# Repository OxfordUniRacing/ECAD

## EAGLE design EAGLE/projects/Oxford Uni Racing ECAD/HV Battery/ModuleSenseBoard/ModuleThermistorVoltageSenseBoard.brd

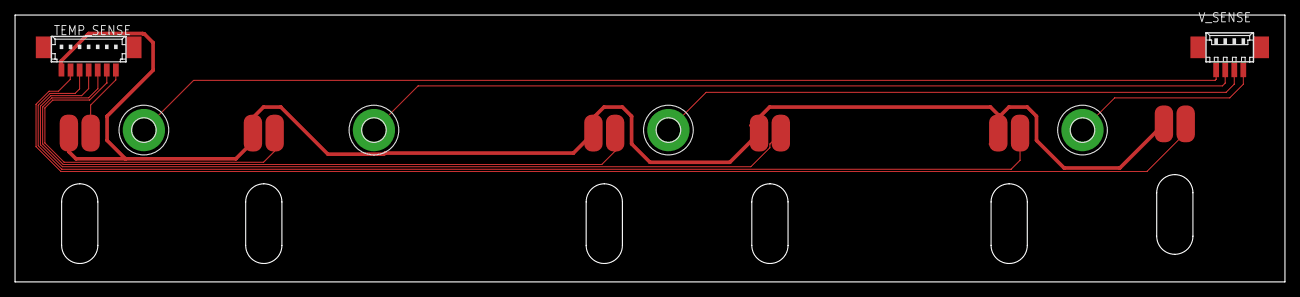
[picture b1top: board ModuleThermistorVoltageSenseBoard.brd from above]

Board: 2 copper layers, 175.3 x 36.8 mm, 12 parts (0 on the bottom side), 11 nets.

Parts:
T1, T2, T3, T4, T5, T6: THERMISTOR_CUTOUT
TEMP_SENSE: 53398-07
V1+, V1-, V2+, V3+: MOUNT-PAD-ROUND3.2; 3,2-PAD
V_SENSE: 53261-04

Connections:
GND: T1.1, T2.1, T3.1, T4.1, T5.1, T6.1, TEMP_SENSE.7
unnamed: T2.2, TEMP_SENSE.2
unnamed: T3.2, TEMP_SENSE.3
unnamed: T4.2, TEMP_SENSE.4
unnamed: T5.2, TEMP_SENSE.5
unnamed: T6.2, TEMP_SENSE.6
TSENSE1: T1.2, TEMP_SENSE.1
V1+: V1+.B3,2, V_SENSE.2
V1-: V1-.B3,2, V_SENSE.1
V2+: V2+.B3,2, V_SENSE.3
V3+: V3+.B3,2, V_SENSE.4

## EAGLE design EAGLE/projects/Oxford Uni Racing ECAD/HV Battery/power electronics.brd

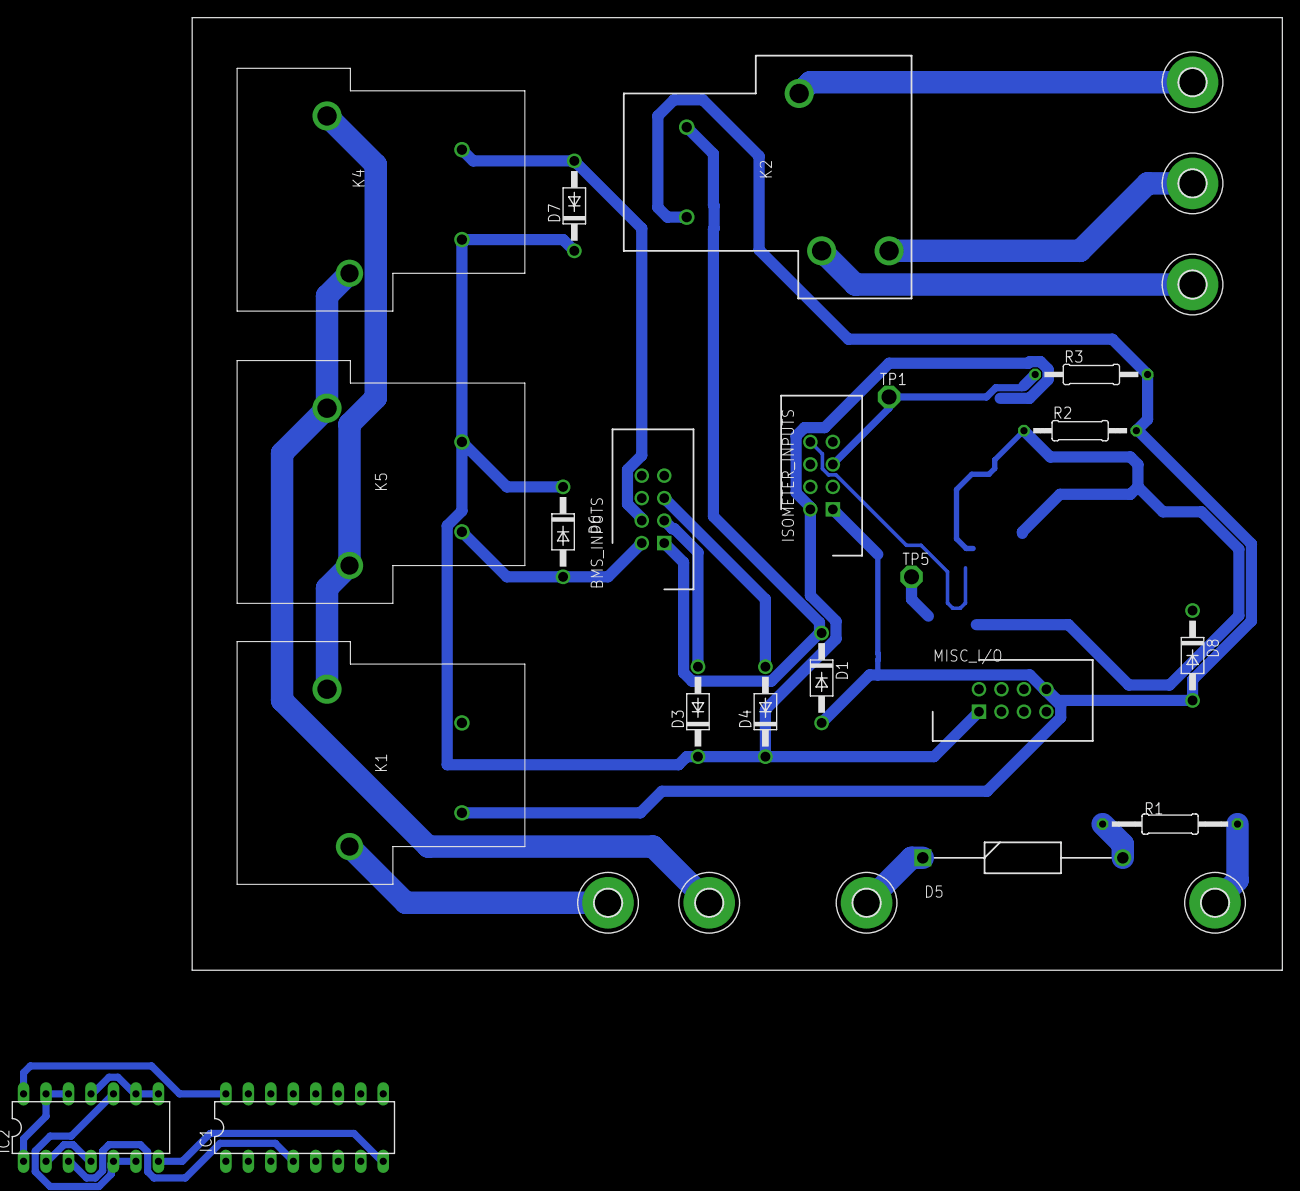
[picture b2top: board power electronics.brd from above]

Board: 2 copper layers, 123.2 x 107.6 mm, 28 parts (0 on the bottom side), 25 nets.

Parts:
BMS_INPUTS: T821108A1S100CEU; HDRV8W64P254_2X4_1778X895X915P
D1, D3, D4, D6, D7, D8: 1N4004; DO41-10
D5: 1N5369BRLG; DIOAD2260W109L864D349
EMSDC: MOUNT-PAD-ROUND3.0; 3,0-PAD
EMSDC_POSAIR-: MOUNT-PAD-ROUND3.0; 3,0-PAD
EMSDC_PRECHARGERELAY-: MOUNT-PAD-ROUND3.0; 3,0-PAD
EMSDC_TSMS+: MOUNT-PAD-ROUND3.0; 3,0-PAD
EMSDC_TSMS-: MOUNT-PAD-ROUND3.0; 3,0-PAD
HV+: MOUNT-PAD-ROUND3.0; 3,0-PAD
HV_INDICATOR: MOUNT-PAD-ROUND3.0; 3,0-PAD
IC1: 4043N; DIL16
IC2: 4001N; DIL14
ISOMETER_INPUTS: T821108A1S100CEU; HDRV8W64P254_2X4_1778X895X915P
K1, K4, K5: T9AS1D12-48=T9A; T9AS1D1248T9A
K2: T9AS5D12-12=T9A; T9AS1D12
MISC_I/O: T821108A1S100CEU; HDRV8W64P254_2X4_1778X895X915P
R1: 3.3K; 0207/15
R2, R3: 2.2K; 0207/12
TP1, TP5: TPSPAD1-17; P1-17

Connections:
+12V: D3.C, D4.C, D6.C, D7.C, IC1.5, ISOMETER_INPUTS.2, K4.2, K5.1, MISC_I/O.1
CHG_SAFE: BMS_INPUTS.2, D6.A, K5.2
DISCHARGE_ENABLE: BMS_INPUTS.4, D7.A, K4.1
EMSDC_IMD+: K1.4, K4.4, K5.3
GND: D1.A, D8.A, IC1.3, ISOMETER_INPUTS.1, K1.2, K2.5, MISC_I/O.8, R2.2, R3.2
unnamed: EMSDC_TSMS-.B3,0, K2.1
unnamed: EMSDC_POSAIR-.B3,0, K2.3
unnamed: EMSDC_PRECHARGERELAY-.B3,0, K2.2
unnamed: EMSDC_TSMS+.B3,0, K4.3, K5.4
unnamed: D5.1, HV+.B3,0
unnamed: BMS_INPUTS.3, D3.A
unnamed: D5.2, R1.2
unnamed: BMS_INPUTS.5, D4.A
unnamed: HV_INDICATOR.B3,0, R1.1
unnamed: ISOMETER_INPUTS.5, R3.1, TP1.TP
unnamed: IC2.1, IC2.12, IC2.13, ISOMETER_INPUTS.8, R2.1, TP5.TP
unnamed: IC2.8, IC2.9, IC2.11
unnamed: IC2.5, IC2.6, IC2.10
unnamed: IC2.2, IC2.4
unnamed: D8.C, IC1.2, K1.1
unnamed: EMSDC.B3,0, K1.3
unnamed: IC1.4, IC2.3
PRECHARGE/SS_SELECT: BMS_INPUTS.1, D1.C, K2.4
VDD: IC1.16, IC2.14
VSS: IC1.8, IC2.7

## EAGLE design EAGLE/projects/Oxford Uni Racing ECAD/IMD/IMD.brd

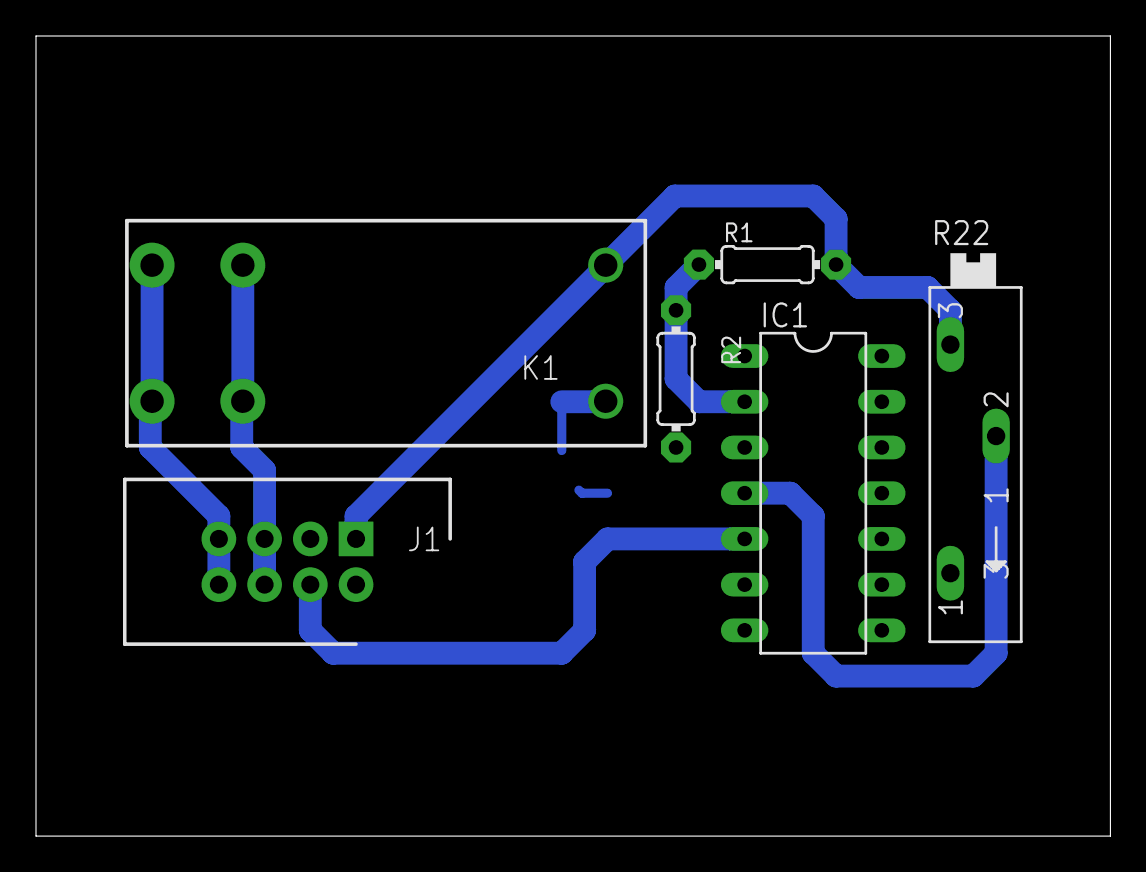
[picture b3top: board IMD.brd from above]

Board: 2 copper layers, 59.7 x 44.5 mm, 7 parts (1 on the bottom side), 9 nets.

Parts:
BR_LIGHTS_TR: IRLML2502GTRPBF; SOT23
IC1: LM2901N; DIL14
J1: HDRV8W64P254_2X4_1778X895X915P
K1: RT444012; RT2N/O
R1, R2: 1K; 0204/7
R22: 1K; SP19L

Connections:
12V: J1.1, K1.A1, R1.2, R22.E
ASS1: J1.7, J1.8, K1.14, K1.24
ASS2: J1.5, J1.6, K1.11, K1.21
GND: BR_LIGHTS_TR.2, IC1.6, IC1.7, IC1.8, IC1.9, IC1.10, IC1.11, J1.2, R22.A
IMD_REF: IC1.5, J1.4
unnamed: IC1.2, R1.1, R2.1
unnamed: BR_LIGHTS_TR.1, R2.2
unnamed: IC1.4, R22.S
unnamed: BR_LIGHTS_TR.3, K1.A2

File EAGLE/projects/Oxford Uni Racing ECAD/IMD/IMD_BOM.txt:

Partlist exported from C:/Users/Ruzhev/Desktop/Formula Student/GIT/ECAD/EAGLE/projects/Oxford Uni Racing ECAD/IMD/IMD.sch at 05/03/2019 15:14

Qty Value           Device           Package                        Parts        Description                                                                                                               
1                   T821108A1S100CEU HDRV8W64P254_2X4_1778X895X915P J1           HEADER, VERTICAL, 2.54MM, 8WAY Amphenol T821 Series, 2.54mm Pitch 8 Way 2 Row Straight PCB Header, Solder Termination, 3A 
2   1K              R-US_0204/7      0204/7                         R1, R2       RESISTOR, American symbol                                                                                                 
1   1K              TRIM_EU-B90P     SP19L                          R22          POTENTIOMETER                                                                                                             
1   IRLML2502GTRPBF MOSFET-NREFLOW   SOT23                          BR_LIGHTS_TR N-Channel Mosfet                                                                                                          
1   LM2901N         LM2901N          DIL14                          IC1          COMPARATOR                                                                                                                
1   RT444012        RT444012         RT2N/O                         K1           Power PCB Relay SCHRACK

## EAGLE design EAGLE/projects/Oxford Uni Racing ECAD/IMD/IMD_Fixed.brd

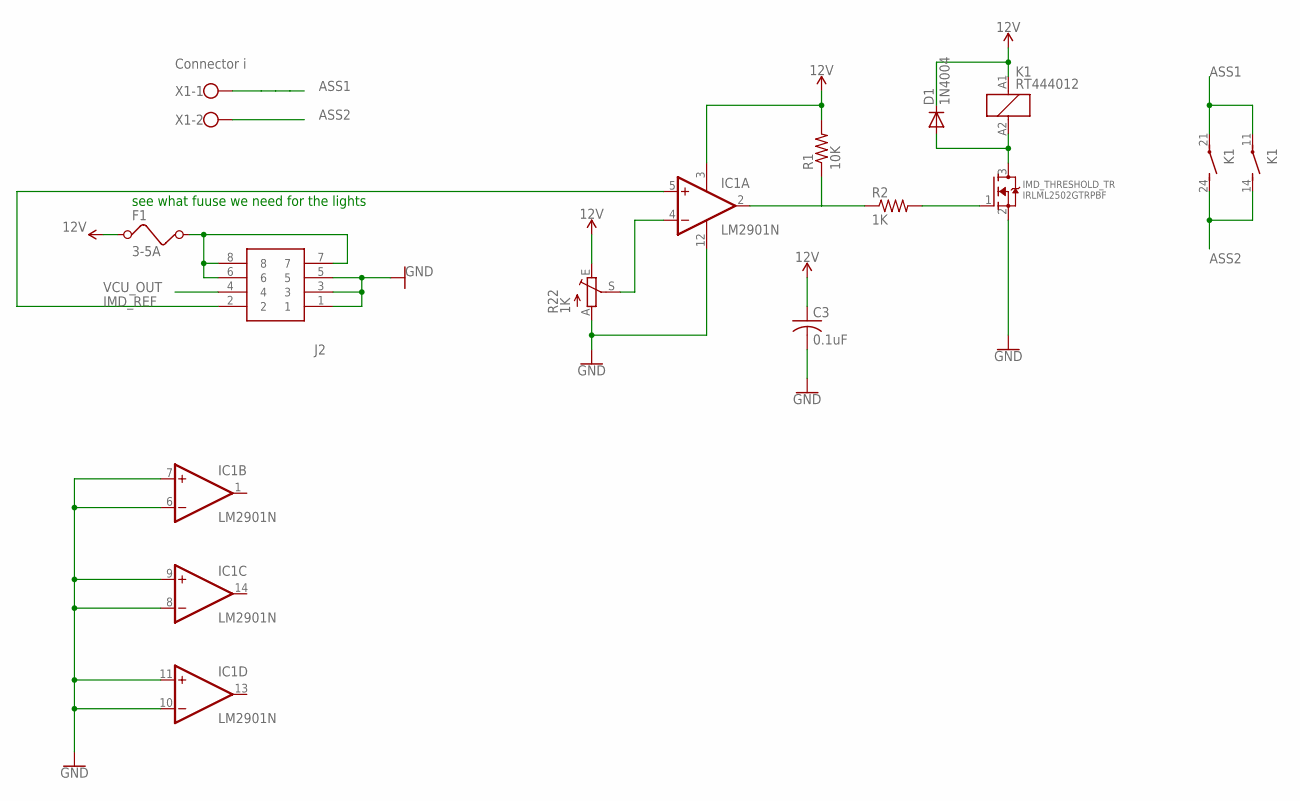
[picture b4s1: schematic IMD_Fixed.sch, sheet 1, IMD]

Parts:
C3: 0.1uF; C050-024X044
D1: 1N4004; DO41-10
F1: 3-5A; FUSE
IC1: LM2901N; DIL14
IMD_THRESHOLD_TR: IRLML2502GTRPBF; SOT23
J2: T821108A1S100CEU; HDRV8W64P254_2X4_1778X895X915P
K1: RT444012; RT2N/O
R1: 10K; R0805
R2: 1K; R0805
R22: 1K; SP19L
X1: Connector i; W237-102

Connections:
12V: C3.1, D1.C, F1.1, IC1.3 (V+), K1.A1 (1), R1.2, R22.E; also elsewhere on the board
ASS1: K1.11, K1.21, X1.1
ASS2: K1.14 (S), K1.24 (S), X1.2
GND: C3.2, IC1.6 (-IN), IC1.7 (+IN), IC1.8 (-IN), IC1.9 (+IN), IC1.10 (-IN), IC1.11 (+IN), IC1.12 (V-), IMD_THRESHOLD_TR.2 (S), J2.1, J2.3, J2.5, R22.A; also elsewhere on the board
IMD_REF: IC1.5 (+IN), J2.2
unnamed: IC1.2 (OUT), R1.1, R2.1
unnamed: F1.2, J2.6, J2.7, J2.8
unnamed: IMD_THRESHOLD_TR.1 (G), R2.2
unnamed: IC1.4 (-IN), R22.S
unnamed: D1.A, IMD_THRESHOLD_TR.3 (D), K1.A2 (2)
VCU_OUT: J2.4; also elsewhere on the board

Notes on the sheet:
see what fuuse we need for the lights

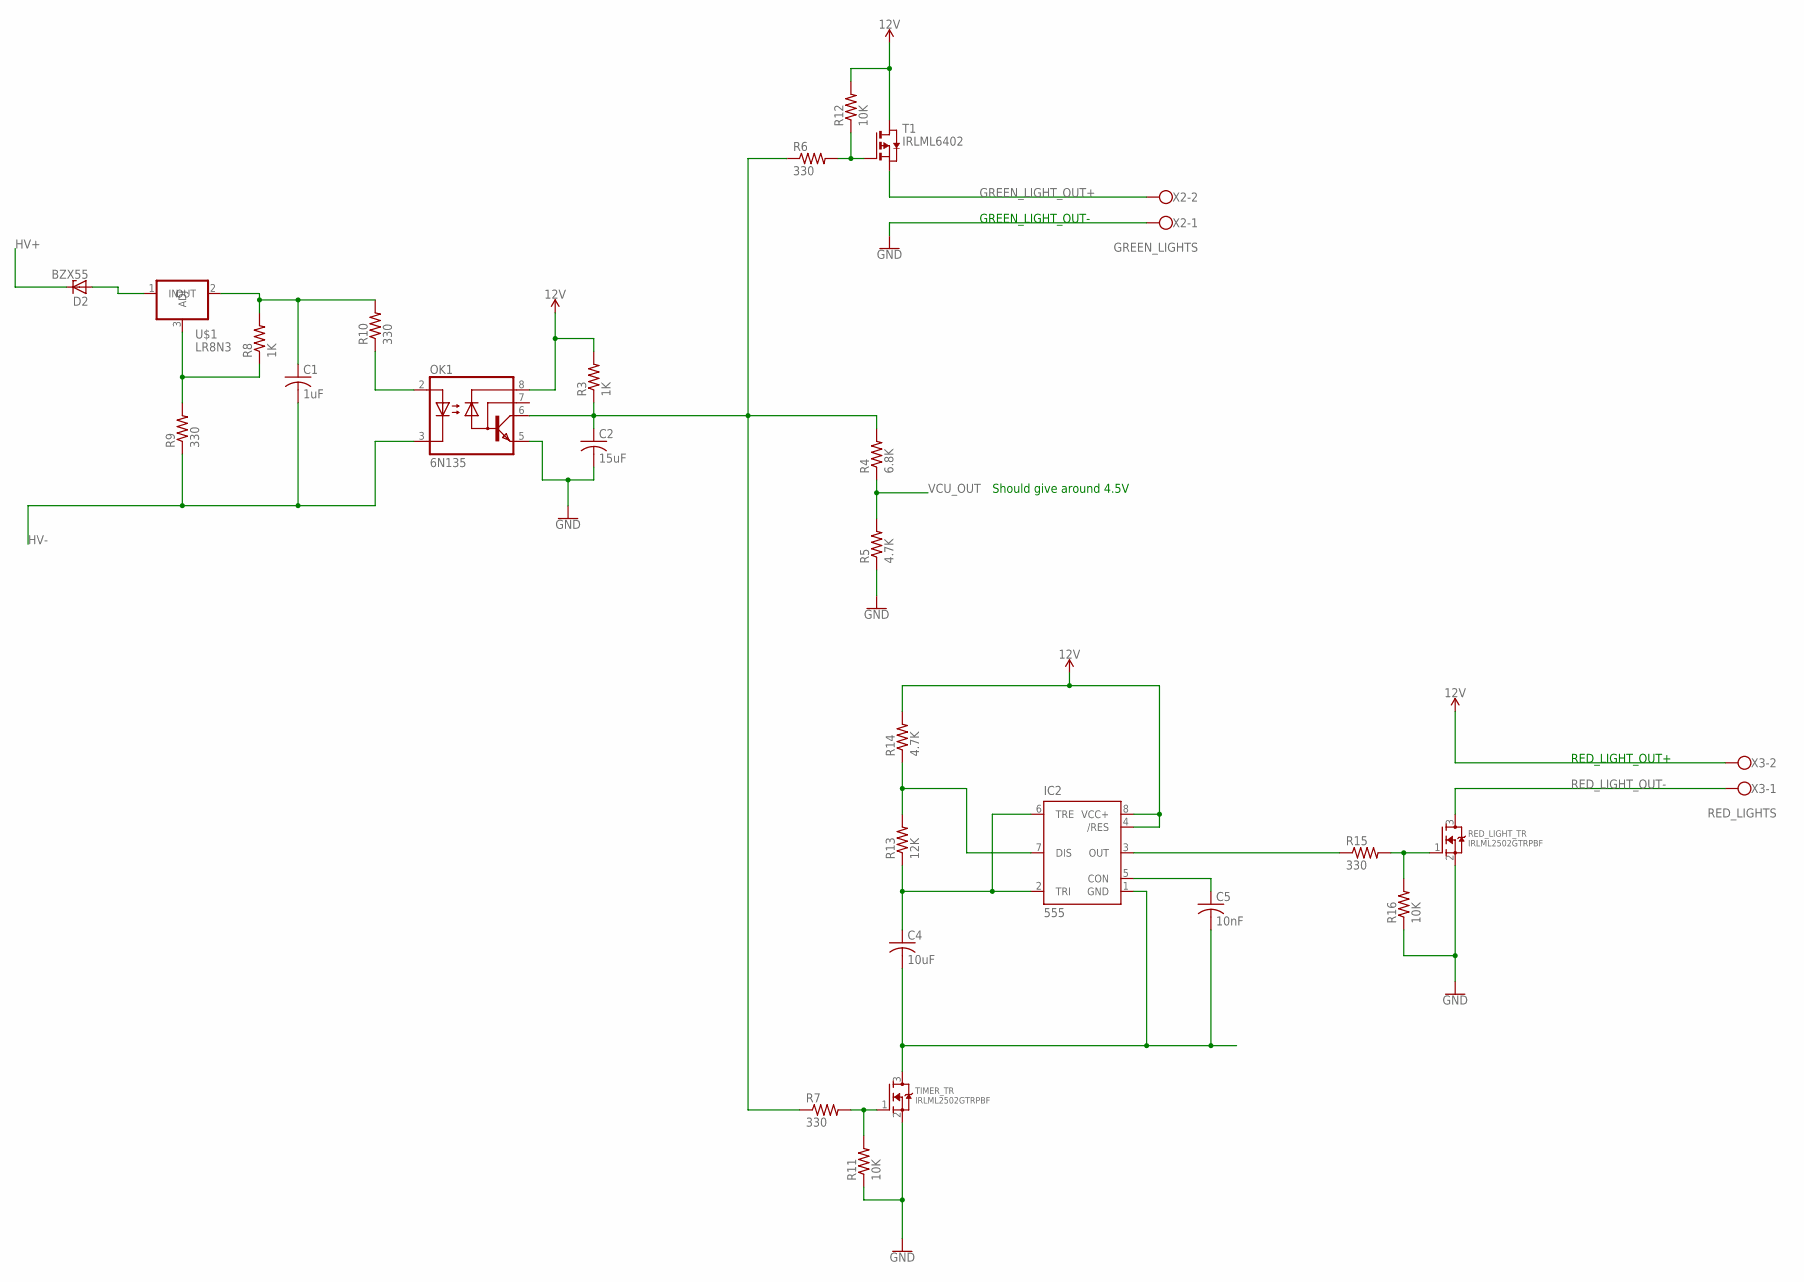
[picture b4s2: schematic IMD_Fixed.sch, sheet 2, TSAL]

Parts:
C1: 1uF; C050-024X044
C2: 15uF; C050-024X044
C4: 10uF; C050-024X044
C5: 10nF; C050-024X044
D2: BZX55; DO35Z10
IC2: 555; DIP08-KIT
OK1: 6N135; DIL08
R3: 1K; M0805
R4: 6.8K; M0805
R5, R14: 4.7K; M0805
R6, R7, R15: 330; M0805
R8: 1K; 0204/7
R9, R10: 330; 0204/7
R11, R12, R16: 10K; M0805
R13: 12K; M0805
RED_LIGHT_TR: IRLML2502GTRPBF; SOT23
T1: IRLML6402; SOT-23
TIMER_TR: IRLML2502GTRPBF; SOT23
U$1: LR8N3; N3
X2: GREEN_LIGHTS; W237-102
X3: RED_LIGHTS; W237-102

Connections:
12V: IC2.4 (/RES), IC2.8 (VCC+), OK1.8 (VCC), R3.2, R12.2, R14.2, T1.1 (D), X3.2; also elsewhere on the board
GND: C2.2, OK1.5 (GND), R5.1, R11.1, R16.1, RED_LIGHT_TR.2 (S), TIMER_TR.2 (S), X2.1; also elsewhere on the board
GREEN_LIGHT_OUT+: T1.2 (S), X2.2
HV+: D2.C
HV-: C1.2, OK1.3 (C), R9.1
unnamed: D2.A, U$1.1 (IN)
unnamed: R8.1, R9.2, U$1.3 (ADJ)
unnamed: OK1.2 (A), R10.1
unnamed: C1.1, R8.2, R10.2, U$1.2 (OUT)
unnamed: C2.1, OK1.6 (VO), R3.1, R4.2, R6.1, R7.1
unnamed: R6.2, R12.1, T1.3 (G)
unnamed: R7.2, R11.2, TIMER_TR.1 (G)
unnamed: C4.2, C5.2, IC2.1 (GND), TIMER_TR.3 (D)
unnamed: R15.2, R16.2, RED_LIGHT_TR.1 (G)
unnamed: IC2.7 (DIS), R13.2, R14.1
unnamed: C4.1, IC2.2 (TRI), IC2.6 (TRE), R13.1
unnamed: C5.1, IC2.5 (CON)
unnamed: IC2.3 (OUT), R15.1
RED_LIGHT_OUT-: RED_LIGHT_TR.3 (D), X3.1
VCU_OUT: R4.1, R5.2; also elsewhere on the board

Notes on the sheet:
Should give around 4.5V
GREEN_LIGHT_OUT-
RED_LIGHT_OUT+

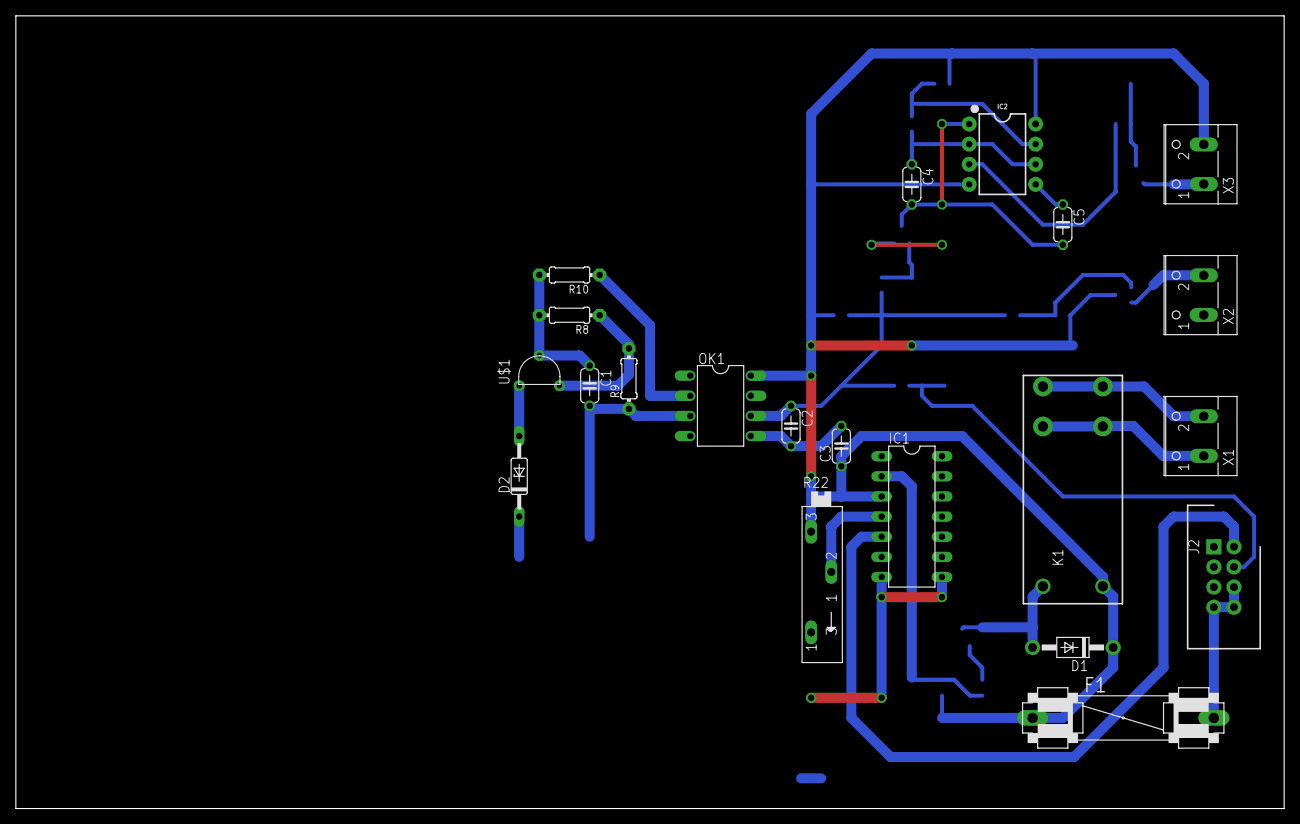
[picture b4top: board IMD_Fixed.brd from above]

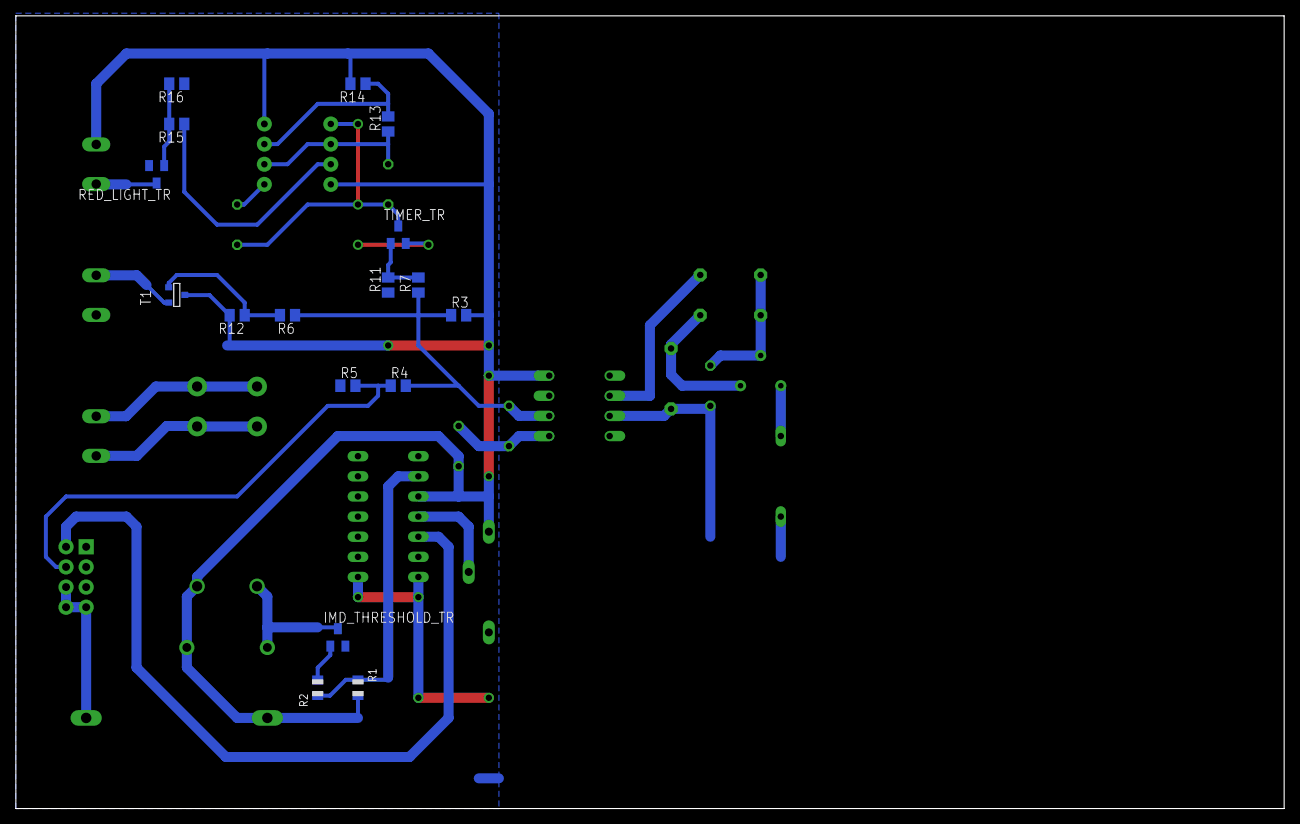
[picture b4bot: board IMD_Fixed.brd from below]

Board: 2 copper layers, 160.0 x 100.0 mm, 38 parts (17 on the bottom side), 27 nets.

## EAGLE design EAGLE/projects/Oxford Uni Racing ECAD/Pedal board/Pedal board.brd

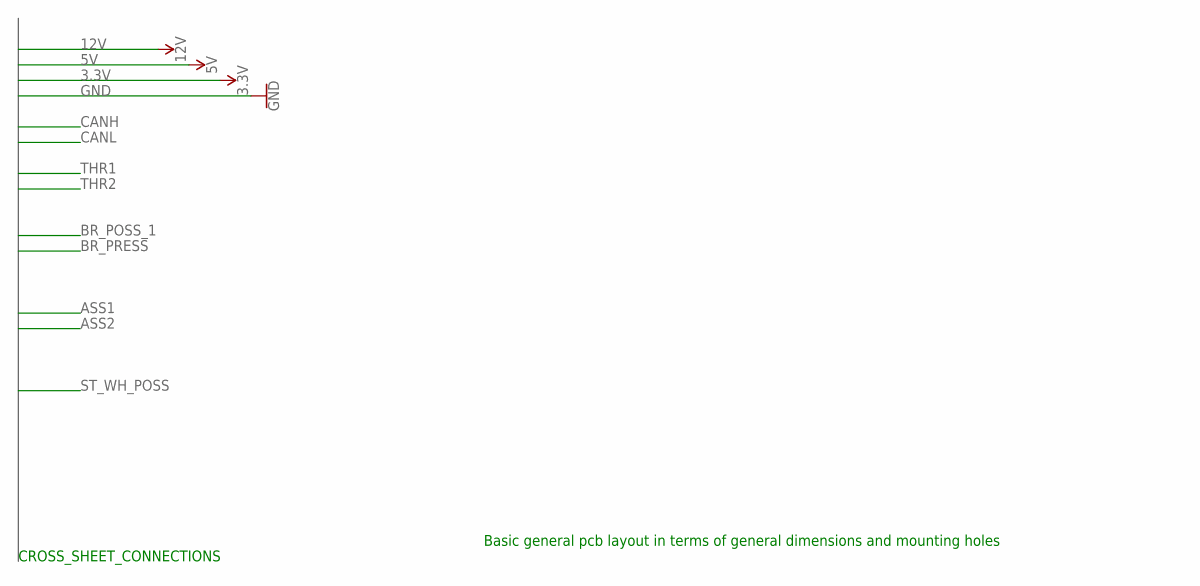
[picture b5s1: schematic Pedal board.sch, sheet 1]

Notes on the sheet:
CROSS_SHEET_CONNECTIONS
Basic general pcb layout in terms of general dimensions and mounting holes

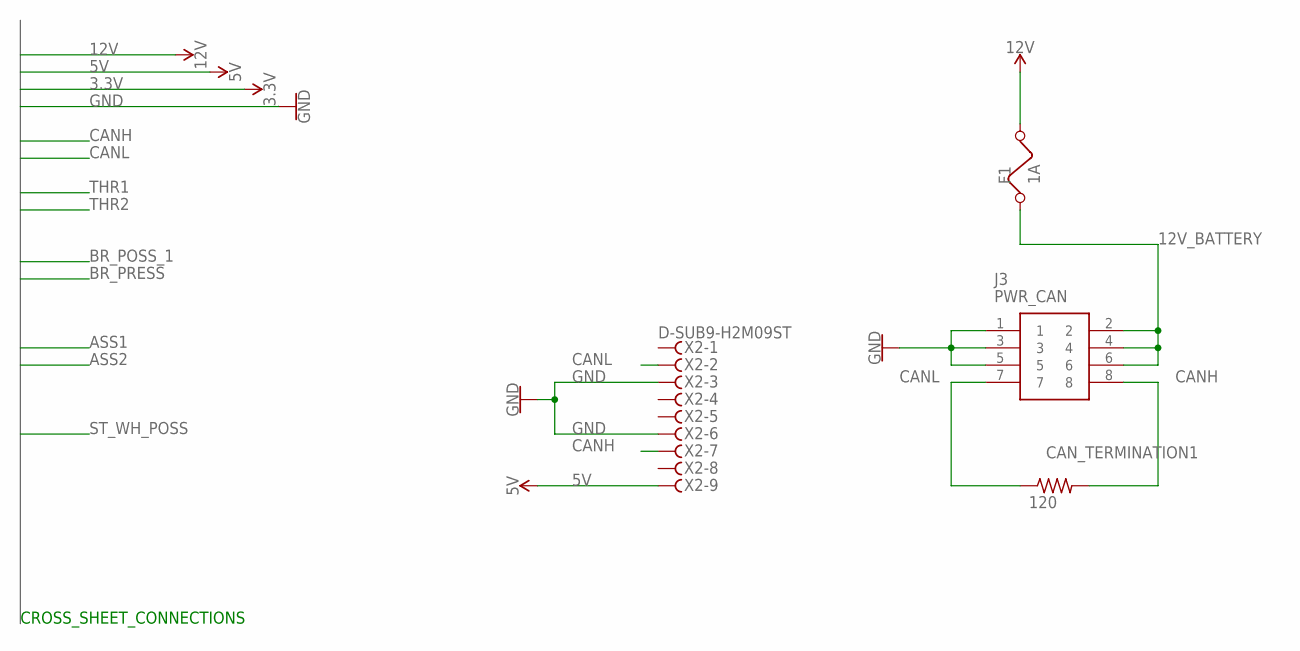
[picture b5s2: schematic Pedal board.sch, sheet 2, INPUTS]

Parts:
CAN_TERMINATION1: 120; R0805
F1: 1A; FUSE
J3: PWR_CAN; HDRV8W64P254_2X4_1778X895X915P
X2: D-SUB9-H2M09ST; H2M09ST

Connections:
5V: X2.9; also elsewhere on the board
12V: F1.2; also elsewhere on the board
12V_BATTERY: F1.1, J3.2, J3.4, J3.6
CANH: CAN_TERMINATION1.2, J3.8, X2.7; also elsewhere on the board
CANL: CAN_TERMINATION1.1, J3.7, X2.2; also elsewhere on the board
GND: J3.1, J3.3, J3.5, X2.3, X2.6; also elsewhere on the board

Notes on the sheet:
CROSS_SHEET_CONNECTIONS

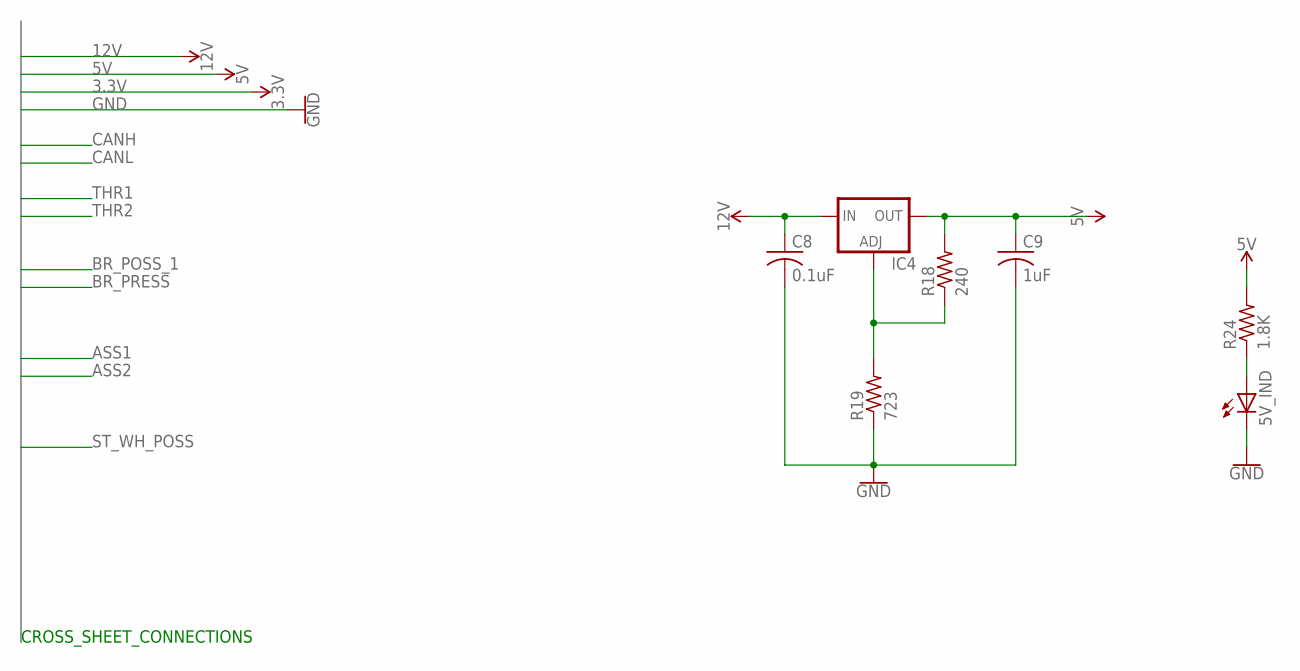
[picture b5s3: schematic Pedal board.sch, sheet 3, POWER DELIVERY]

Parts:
5V_IND: LED3MM
C8: 0.1uF; C050-025X075
C9: 1uF; C050-025X075
IC4: LM317TS; 317TS
R18: 240; R0805
R19: 723; R0805
R24: 1.8K; R0805

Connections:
5V: C9.1, IC4.2 (OUT), R18.2, R24.2; also elsewhere on the board
12V: C8.1, IC4.3 (IN); also elsewhere on the board
GND: 5V_IND.K (C), C8.2, C9.2, R19.1; also elsewhere on the board
unnamed: 5V_IND.A, R24.1
unnamed: IC4.1 (ADJ), R18.1, R19.2

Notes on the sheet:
CROSS_SHEET_CONNECTIONS

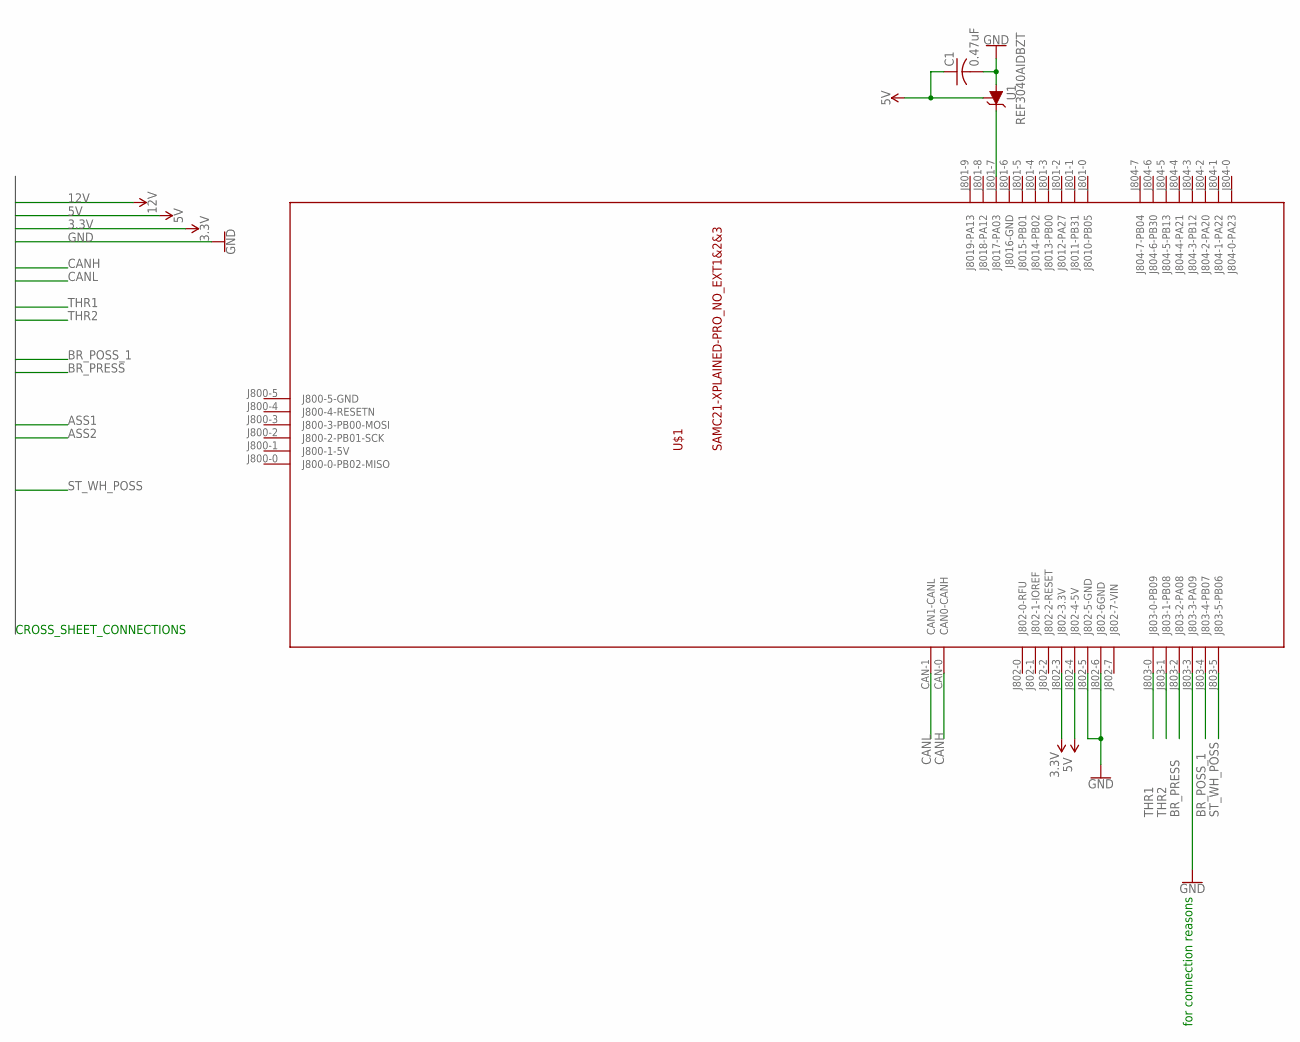
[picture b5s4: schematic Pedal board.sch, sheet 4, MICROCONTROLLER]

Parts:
C1: 0.47uF; C050-024X044
U1: REF3040AIDBZT; SOT23-3
U$1: SAMC21-XPLAINED-PRO_NO_EXT1&2&3

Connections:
3.3V: U$1.J802-3 (J802-3.3V); also elsewhere on the board
5V: C1.1, U1.1 (ADJ), U$1.J802-4 (J802-4-5V); also elsewhere on the board
BR_POSS_1: U$1.J803-4 (J803-4-PB07); also elsewhere on the board
BR_PRESS: U$1.J803-2 (J803-2-PA08); also elsewhere on the board
CANH: U$1.CAN-0 (CAN0-CANH); also elsewhere on the board
CANL: U$1.CAN-1 (CAN1-CANL); also elsewhere on the board
GND: C1.2, U1.3 (A), U$1.J802-5 (J802-5-GND), U$1.J802-6 (J802-6GND), U$1.J803-3 (J803-3-PA09); also elsewhere on the board
unnamed: U1.2 (C), U$1.J801-7 (J8017-PA03)
ST_WH_POSS: U$1.J803-5 (J803-5-PB06); also elsewhere on the board
THR1: U$1.J803-0 (J803-0-PB09); also elsewhere on the board
THR2: U$1.J803-1 (J803-1-PB08); also elsewhere on the board

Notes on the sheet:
CROSS_SHEET_CONNECTIONS
for connection reasons

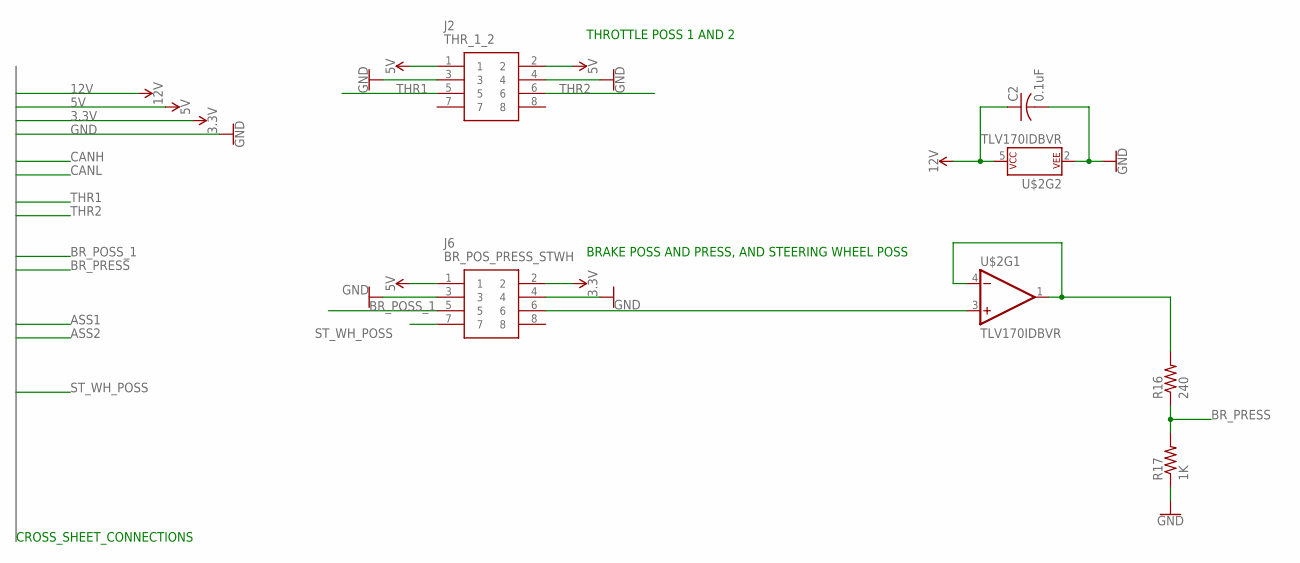
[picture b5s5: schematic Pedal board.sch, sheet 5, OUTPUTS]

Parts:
C2: 0.1uF; C050-024X044
J2: THR_1_2; HDRV8W64P254_2X4_1778X895X915P
J6: BR_POS_PRESS_STWH; HDRV8W64P254_2X4_1778X895X915P
R16: 240; R0805
R17: 1K; R0805
U$2: TLV170IDBVR; SOT23-5

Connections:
3.3V: J6.2; also elsewhere on the board
5V: J2.1, J2.2, J6.1; also elsewhere on the board
12V: C2.1, U$2.5 (P$V+); also elsewhere on the board
BR_POSS_1: J6.5; also elsewhere on the board
BR_PRESS: R16.1, R17.2; also elsewhere on the board
GND: C2.2, J2.3, J2.4, J6.3, J6.4, R17.1, U$2.2 (P$V-); also elsewhere on the board
unnamed: R16.2, U$2.1 (OUT), U$2.4 (-IN)
unnamed: J6.6, U$2.3 (+IN)
ST_WH_POSS: J6.7; also elsewhere on the board
THR1: J2.5; also elsewhere on the board
THR2: J2.6; also elsewhere on the board

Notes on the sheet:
CROSS_SHEET_CONNECTIONS
THROTTLE POSS 1 AND 2
BRAKE POSS AND PRESS, AND STEERING WHEEL POSS

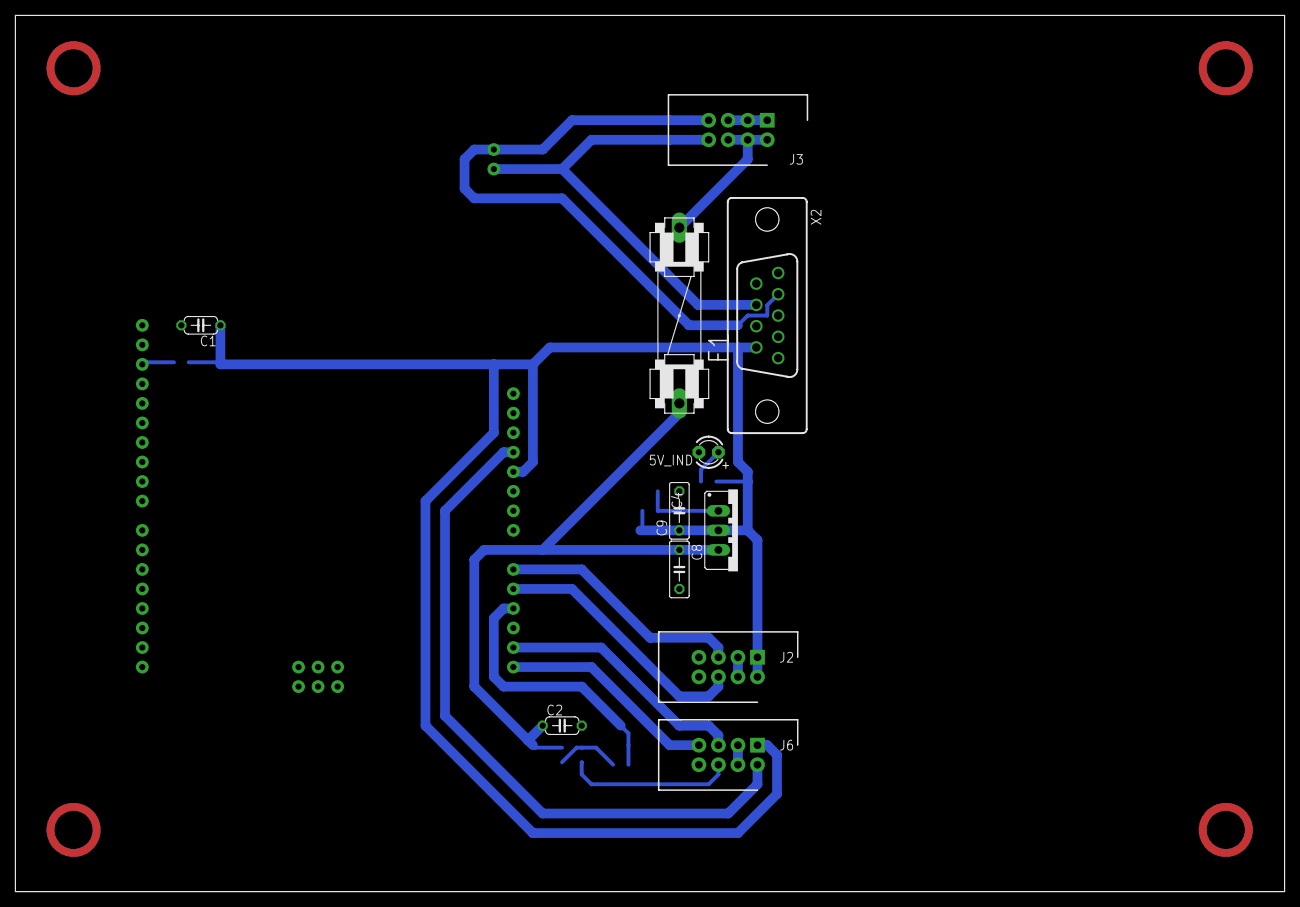
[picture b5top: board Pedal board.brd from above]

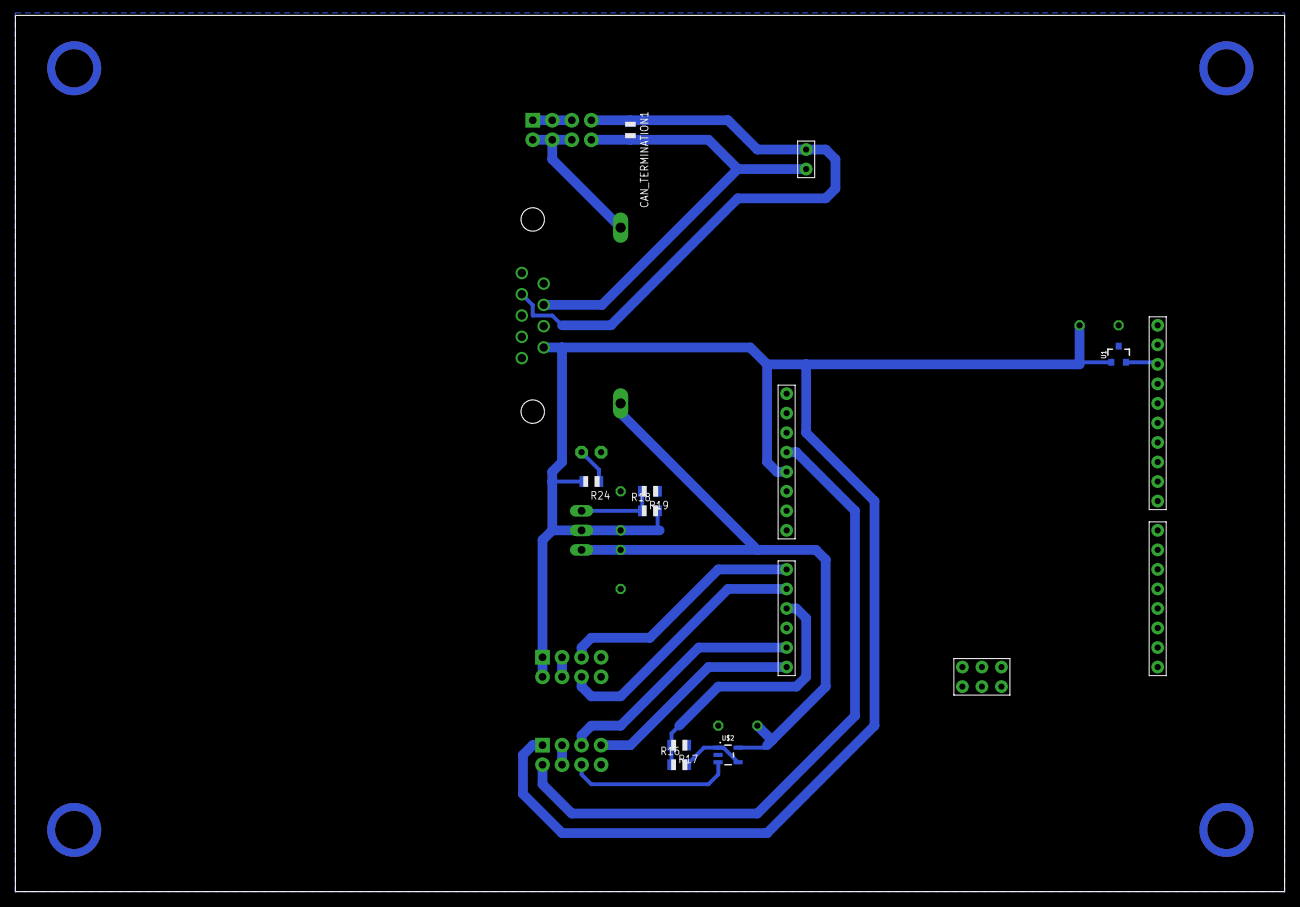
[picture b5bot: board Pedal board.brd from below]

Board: 2 copper layers, 165.1 x 114.0 mm, 20 parts (9 on the bottom side), 17 nets.

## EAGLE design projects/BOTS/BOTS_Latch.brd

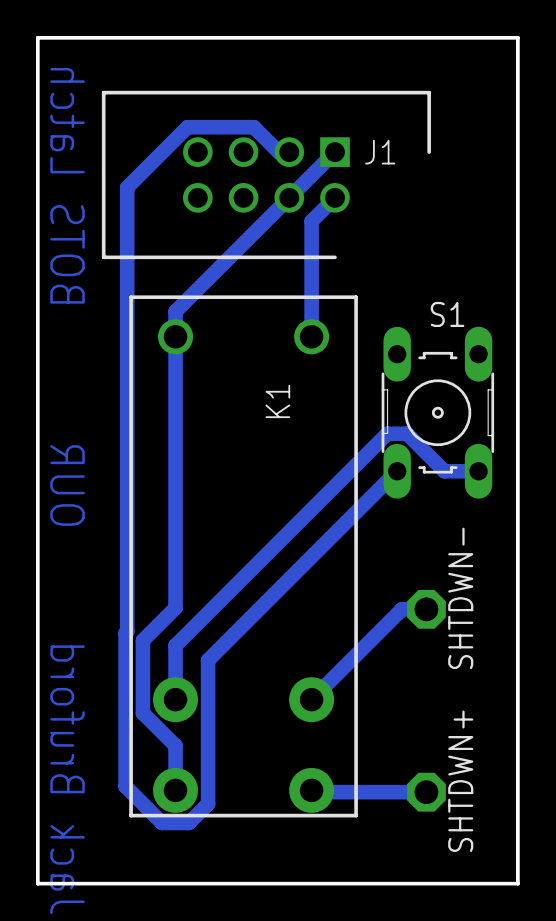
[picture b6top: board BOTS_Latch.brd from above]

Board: 2 copper layers, 26.7 x 47.0 mm, 5 parts (0 on the bottom side), 6 nets.

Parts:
J1: T821108A1S100CEU; HDRV8W64P254_2X4_1778X895X915P
K1: RT444012; RT2N/O
S1: B3F-10XX
SHTDWN+: TPPAD1-13; P1-13
SHTDWN-: TPPAD1-13; P1-13

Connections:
+12V: J1.1, J1.4, K1.14, K1.A1
GND: J1.2, K1.A2
unnamed: K1.11, S1.2
unnamed: J1.3, S1.4
unnamed: K1.24, SHTDWN+.TP
unnamed: K1.21, SHTDWN-.TP

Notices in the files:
parts and their libraries:
SparkFun-IC-Special-Function: Licensing: Creative Commons ShareAlike 4.0 International - https://creativecommons.org/licenses/by-sa/4.0
